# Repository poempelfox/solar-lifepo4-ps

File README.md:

# Solar-LiFePO4 power-supply module

## Intro

The goal of this project is to build a power-supply
module with a standard 26650 LiFePO4 battery that can
be powered from a small solar panel and will take
care of all the handling of the battery, including
protection, for you.
The battery is put into a battery holder that is
directly on the board.

Essentially, this is trying to build something
very similiar to Waveshares "Solar Power Manager",
just using LiFePO4 instead of Li-Ion. The
downside is the smaller energy density. The upside
is that LiFePO4 is much much more stable and simply
can not spontanously burst into flames.

I would have preferred to not design this myself,
because I'm really out of my depth here. However,
I was completely unable to find something ready-made
to buy, and even my search for (open-source-)projects
that had already built something like that proved
fruitless. Of course, after I was two-thirds finished,
I accidently found the
[LiFePO4 Solar Charger by Stefan Wagner](https://github.com/wagiminator/Power-Boards/blob/master/Solar_Charger/readme.md)
that would have been almost exactly what I was looking
for, but by then it was too late.

During construction,
[a blog entry by Malte Poeggel and his design files](https://www.maltepoeggel.de/?site=solar-mppt-cn3722&lang=en)
was a great inspiration, because it uses the same
main charge controller (CN3722) and so I had a known-working
design to start from.

## Features

Input is meant to be a 12V solar panel. Maximum input
voltage for the circuit is 25V, so the solar panel
voltage without any load should be fine.

The board has a slot for a standard 26650 LiFePO4
flat top unprotected battery. The protection circuit
(HY2112) is on the board and protects against
short circuits, overcharge, and deep discharge.
There is also protection against charging below
0°C (which can damage LiFePO4 batteries), but that
is done by the main CN3722 charge controller which has
a Thermistor connected for that purpose. Note that
because the Thermistor is on the board and not
directly attached to the battery, this may be
insufficient for some use cases where large
temperature differences between board and battery
can occour.

Charge current is capped at 1A.

There is a regulated 5V output through an ultra-
efficient MAX17224 boost converter. Output voltage can
be reconfigured to between 3.4 - 5V by removing and
soldering in another resistor. However, because this
is a boost converter, you cannot (reliably) go below
3.4V - the minimum voltage is (battery voltage - 0.2V).
You should be able to pull around 400 mA at 5V or
600 mA at 3.4V out of this - although if you pull this
much current permanently, you'll not last long
with such a small battery.

You can also get the 3.0V - 3.6V output coming from
the battery directly, but that is of course completely
unregulated, and will fluctuate as the battery charges
and discharges. This output is behind the battery
protection circuit, so protected against deep
discharge.

There is a jumper for disabling the boost converter
completely if you don't need the regulated output.
It's also possible to connect a microcontroller to
that jumper and thereby enable/disable the regulated
output in software. A nifty feature of the MAX17224
is that when it is disabled, it completely disconnects
its output, meaning it doesn't care at all if you
feed voltage into that.

Finally, there are two voltage dividers on the board,
with an output that is intended to be connected to
an ADC pin of a microcontroller. A 10 MOhm / 1 MOhm
divider to measure the voltage coming from the solar
panel, and a 10 MOhm / 10 MOhm divider for the battery
voltage. These were selected so that the output
conveniently matches the range of your standard ESP32.

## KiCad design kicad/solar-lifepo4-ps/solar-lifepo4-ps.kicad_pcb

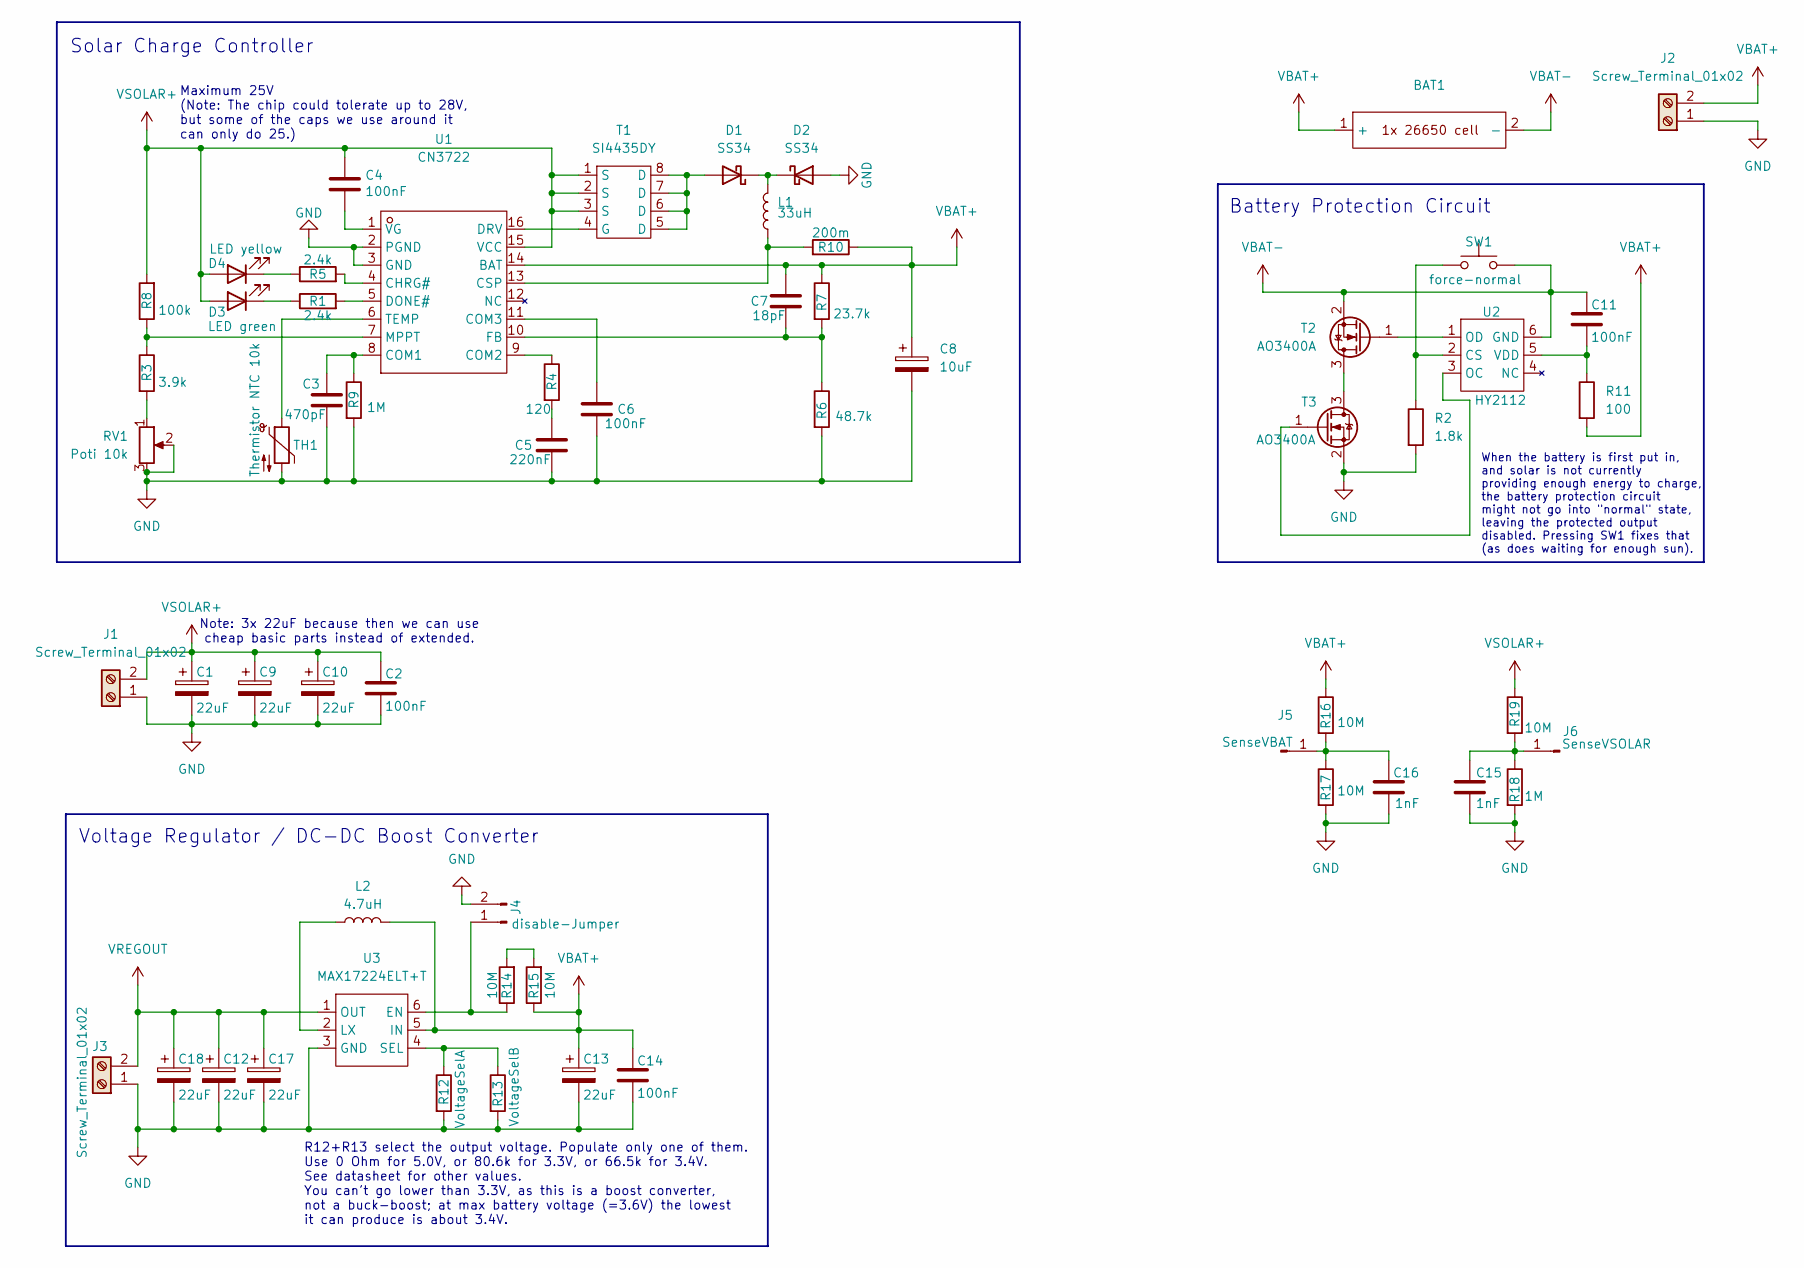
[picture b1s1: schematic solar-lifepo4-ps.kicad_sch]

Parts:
BAT1: batteryholder_keystone_1106-jlcpcb
C1, C9, C10, C12, C13, C17, C18: 22uF; C_0805_2012Metric
C2, C4, C6, C11, C14: 100nF; C_0402_1005Metric
C3: 470pF; C_0603_1608Metric
C5: 220nF; C_0805_2012Metric
C7: 18pF; C_0603_1608Metric
C8: 10uF; C_0805_2012Metric
C15, C16: 1nF; C_0603_1608Metric
D1, D2: SS34; D_SMA
D3: LED green; LED_0805_2012Metric
D4: LED yellow; LED_0805_2012Metric
J1, J2, J3: Screw_Terminal_01x02; TerminalBlock_MetzConnect_Type073_RT02602HBLU_1x02_P5.08mm_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
J4: disable-Jumper; PinHeader_1x02_P2.54mm_Vertical
J5: SenseVBAT; PinHeader_1x01_P2.54mm_Vertical
J6: SenseVSOLAR; PinHeader_1x01_P2.54mm_Vertical
L1: 33uH; L_TDK_SLF12575
L2: 4.7uH; L_Sunlord_MWSA0603S
R1, R5: 2.4k; R_0603_1608Metric
R2: 1.8k; R_0603_1608Metric
R3: 3.9k; R_0603_1608Metric
R4: 120; R_0402_1005Metric
R6: 48.7k; R_0402_1005Metric
R7: 23.7k; R_0402_1005Metric
R8: 100k; R_0402_1005Metric
R9, R18: 1M; R_0402_1005Metric
R10: 200m; R_2512_6332Metric
R11: 100; R_0805_2012Metric
R12: VoltageSelA; R_Axial_DIN0207_L6.3mm_D2.5mm_P10.16mm_Horizontal
R13: VoltageSelB; R_1206_3216Metric
R14, R15, R16, R17, R19: 10M; R_0603_1608Metric
RV1: Poti 10k; Potentiometer_Bourns_3224W_Vertical
SW1: force-normal; SW_Push_1P1T_XKB_TS-1187A
T1: SI4435DY; SOP-8_3.9x4.9mm_P1.27mm
T2, T3: AO3400A; SOT-23
TH1: Thermistor NTC 10k; R_0603_1608Metric
U1: CN3722; TSSOP-16_4.4x5mm_P0.65mm
U2: HY2112; SOT-23-6
U3: MAX17224ELT+T; UDFN-6_L2.0-W2.0-P0.65-BL-1

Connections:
GND: C1.2, C2.2, C3.2, C5.2, C6.2, C8.2, C9.2, C10.2, C12.2, C13.2, C14.2, C15.2, C16.2, C17.2, C18.2, D2.2 (A), J1.1, J2.1, J3.1, J4.2, R2.2, R6.2, R9.2, R12.2, R13.2, R17.2, R18.2, RV1.2, RV1.3, T3.2 (S), TH1.2, U1.2 (PGND), U1.3 (GND), U3.3 (GND)
unnamed: C5.1, R4.2
unnamed: D1.2 (A), T1.5 (D), T1.6 (D), T1.7 (D), T1.8 (D)
unnamed: D1.1 (K), D2.1 (K), L1.2
unnamed: D3.1 (K), R1.1
unnamed: D4.1 (K), R5.1
unnamed: J4.1, R14.1, U3.6 (EN)
unnamed: C16.1, J5.1, R16.2, R17.1
unnamed: C15.1, J6.1, R18.1, R19.2
unnamed: R3.2, RV1.1
unnamed: R14.2, R15.2
unnamed: T1.4 (G), U1.16 (DRV)
unnamed: T2.3 (D), T3.3 (D)
unnamed: T2.1 (G), U2.1 (OD)
unnamed: T3.1 (G), U2.3 (OC)
unnamed: R5.2, U1.4 (CHRG#)
unnamed: C3.1, R9.1, U1.8 (COM1)
unnamed: R4.1, U1.9 (COM2)
unnamed: C6.1, U1.11 (COM3)
unnamed: L1.1, R10.2, U1.13 (CSP)
unnamed: R1.2, U1.5 (DONE#)
unnamed: C7.2, R6.1, R7.2, U1.10 (FB)
unnamed: R3.1, R8.1, U1.7 (MPPT)
unnamed: TH1.1, U1.6 (TEMP)
unnamed: C4.1, U1.1 (VG)
unnamed: R2.1, SW1.1, U2.2 (CS)
unnamed: C11.2, R11.1, U2.5 (VDD)
unnamed: L2.1, U3.2 (LX)
unnamed: R12.1, R13.1, U3.4 (SEL)
VBAT+: BAT1.1 (+), C7.1, C8.1, C13.1, C14.1, J2.2, L2.2, R7.1, R10.1, R11.2, R15.1, R16.1, U1.14 (BAT), U3.5 (IN)
VBAT-: BAT1.2 (-), C11.1, SW1.2, T2.2 (S), U2.6 (GND)
VREGOUT: C12.1, C17.1, C18.1, J3.2, U3.1 (OUT)
VSOLAR+: C1.1, C2.1, C4.2, C9.1, C10.1, D3.2 (A), D4.2 (A), J1.2, R8.2, R19.1, T1.1 (S), T1.2 (S), T1.3 (S), U1.15 (VCC)

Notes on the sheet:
Solar Charge Controller
Maximum 25V (Note: The chip could tolerate up to 28V, but some of the caps we use around it can only do 25.)
Voltage Regulator / DC-DC Boost Converter
Note: 3x 22uF because then we can use cheap basic parts instead of extended.
R12+R13 select the output voltage. Populate only one of them. Use 0 Ohm for 5.0V, or 80.6k for 3.3V, or 66.5k for 3.4V. See datasheet for other values. You can't go lower than 3.3V, as this is a boost converter, not a buck-boost; at max battery voltage (=3.6V) the lowest it can produce is about 3.4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
Battery Protection Circuit
When the battery is first put in, and solar is not currently providing enough energy to charge, the battery protection circuit might not go into "normal" state, leaving the protected output disabled. Pressing SW1 fixes that (as does waiting for enough sun).

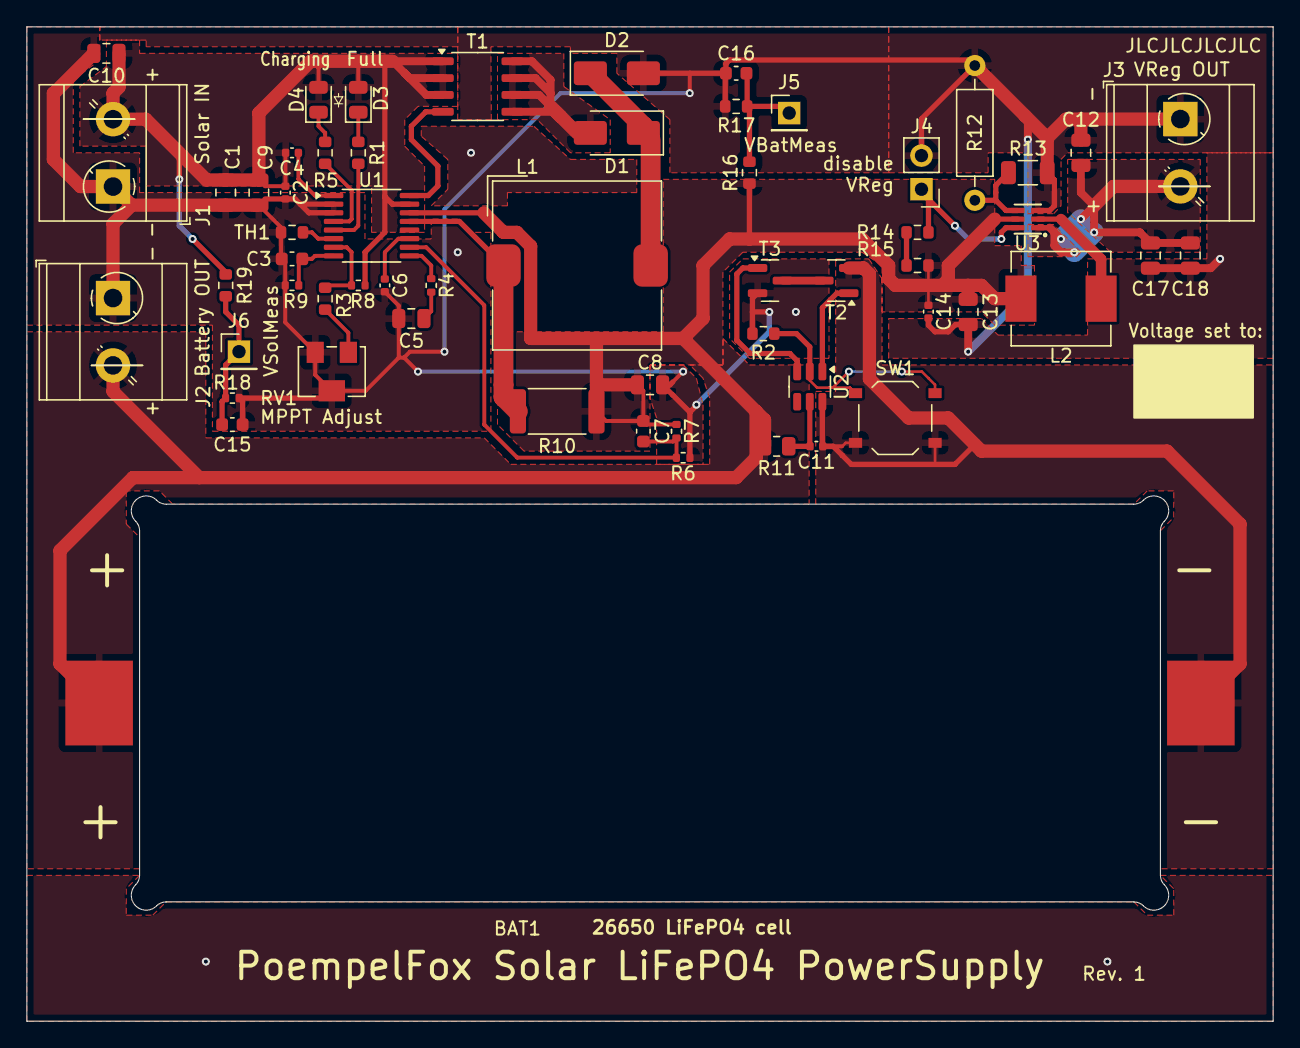
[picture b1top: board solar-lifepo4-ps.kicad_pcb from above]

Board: 2 copper layers, 94.0 x 75.0 mm, 59 parts (0 on the bottom side), 33 nets.

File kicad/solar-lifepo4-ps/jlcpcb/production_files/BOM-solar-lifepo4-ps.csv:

Comment,Designator,Footprint,LCSC
C1,22uF,C_0805_2012Metric,C45783,4372673,0,0
C10,22uF,C_0805_2012Metric,C45783,4372673,0,0
C11,100nF,C_0402_1005Metric,C307331,6856879,0,0
C12,22uF,C_0805_2012Metric,C45783,4372673,0,0
C13,22uF,C_0805_2012Metric,C45783,4372673,0,0
C14,100nF,C_0402_1005Metric,C307331,6856879,0,0
C15,1nF,C_0603_1608Metric,C1588,6040604,0,0
C16,1nF,C_0603_1608Metric,C1588,6040604,0,0
C2,100nF,C_0402_1005Metric,C307331,6856879,0,0
C3,470pF,C_0603_1608Metric,C1620,841712,0,0
C4,100nF,C_0402_1005Metric,C307331,6856879,0,0
C5,220nF,C_0805_2012Metric,C5378,425353,0,0
C6,100nF,C_0402_1005Metric,C307331,6856879,0,0
C7,18pF,C_0603_1608Metric,C1647,224429,0,0
C8,10uF,C_0805_2012Metric,C15850,2210217,0,0
C9,22uF,C_0805_2012Metric,C45783,4372673,0,0
D1,SS34,D_SMA,C8678,997276,0,0
D2,SS34,D_SMA,C8678,997276,0,0
D3,LED green,R_0805_2012Metric,C2297,1323534,0,0
D4,LED yellow,R_0805_2012Metric,C2296,258402,0,0
L1,33uH,L_TDK_SLF12575,C87568,2465,0,0
L2,4.7uH,L_Sunlord_MWSA0603S,C408447,60265,0,0
R1,2.4k,R_0603_1608Metric,C22940,702809,0,0
R10,200m,R_2512_6332Metric,C5375488,8341,0,0
R11,100,R_0805_2012Metric,C17408,6372890,0,0
R13,VoltageSelB,R_1206_3216Metric,C17888,8173888,0,0
R14,10M,R_0603_1608Metric,C7250,225082,0,0
R15,10M,R_0603_1608Metric,C7250,225082,0,0
R16,10M,R_0603_1608Metric,C7250,225082,0,0
R17,10M,R_0603_1608Metric,C7250,225082,0,0
R18,1M,R_0402_1005Metric,C26083,2594408,0,0
R19,10M,R_0603_1608Metric,C7250,225082,0,0
R2,1.8k,R_0603_1608Metric,C4177,435015,0,0
R3,3.9k,R_0603_1608Metric,C23018,817563,0,0
R4,120,R_0402_1005Metric,C25079,547006,0,0
R5,2.4k,R_0603_1608Metric,C22940,702809,0,0
R6,48.7k,R_0402_1005Metric,C103068,47167,0,0
R7,23.7k,R_0402_1005Metric,C82134,14674,0,0
R8,100k,R_0402_1005Metric,C25741,4991595,0,0
R9,1M,R_0402_1005Metric,C26083,2594408,0,0
RV1,Poti 10k,Potentiometer_Bourns_3224W_Vertical,C81348,6722,0,0
T1,SI4435DY,SOP-8_3.9x4.9mm_P1.27mm,C4355022,19004,0,0
T2,AO3400A,SOT-23,C20917,628525,0,0
T3,AO3400A,SOT-23,C20917,628525,0,0
TH1,Thermistor NTC 10k,R_0603_1608Metric,C13564,438964,0,0
U1,CN3722,TSSOP-16_4.4x5mm_P0.65mm,C77905,5126,0,0
U2,HY2112,SOT-23-6,C168763,5680,0,0
U3,MAX17224ELT+T,UDFN-6_L2.0-W2.0-P0.65-BL-1,C2683469,139,0,0

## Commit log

2024-06-18 initial commit - what we produced since saturday.
2024-06-21 still WIP
2024-06-22 more explanations and a small update to the README.
2024-06-22 current state. All the main circuit has been designed now. TODO: voltage divider output to permit a connected MC to measure voltages; fix square hole in PCB because JLCPCB will not be able to manufac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
2024-06-23 rev 0, as it was sent to jlcpcb for production.
2024-07-04 first few fixes after Rev. 0 arrived from the JLCPCB-fab. It seems to be mostly working fine, but I made a few small errors - like forgetting the labels for +/- and using resistor-footprints for the 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
2024-07-06 more labeling on the silkscreen, minor ground plane movement.
2024-07-06 move label so it's not partially hidden by the battery holder when soldered on.
2024-07-06 more description and two pictures.
2024-07-07 add pushbutton to force the battery protection circuit into "normal" mode. When a battery is inserted, but there is not and has never been enough power to actually charge, the battery protection circ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
2024-08-17 add more capacitors at the output of the voltage converter because as it turns out, 1x 22uF was just NOT enough. So we now have 3x 22uF instead.
2024-08-18 do not route traces below the inductor
